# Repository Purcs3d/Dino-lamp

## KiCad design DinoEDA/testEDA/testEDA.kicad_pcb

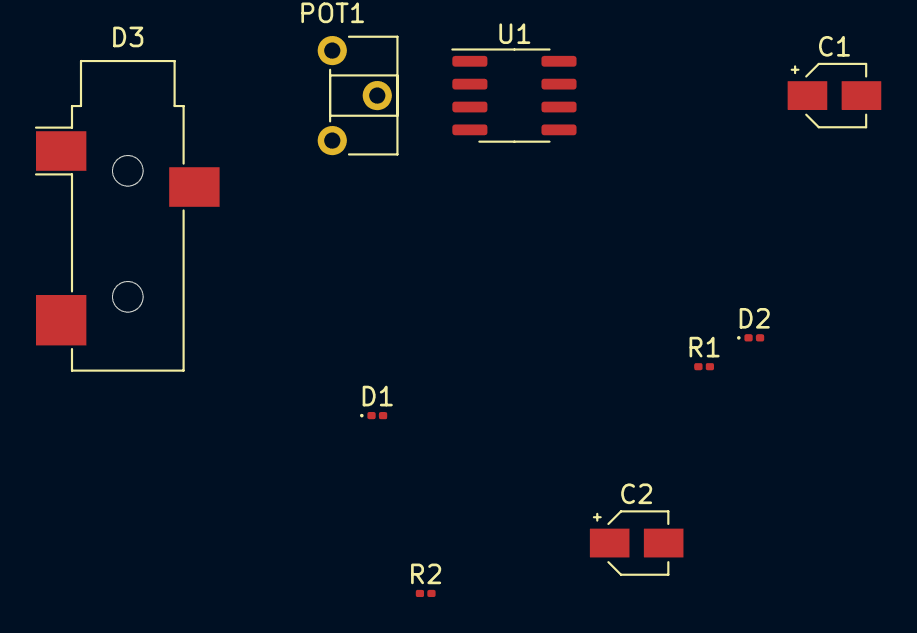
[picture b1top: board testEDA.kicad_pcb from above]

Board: 2 copper layers, 9 parts (0 on the bottom side), 8 nets, no tracks yet.

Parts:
C1: 100nF; CP_Elec_3x5.3
C2: 10nF; CP_Elec_3x5.3
D1, D2: DIODE; D_0201_0603Metric
D3: LED_Series; Jack_3.5mm_CUI_SJ-3523-SMT_Horizontal
POT1: 10K; Potentiometer_ACP_CA6-H2,5_Horizontal
R1: 120; R_0201_0603Metric
R2: 15; R_0201_0603Metric
U1: NE555D; SOIC-8_3.9x4.9mm_P1.27mm

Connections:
+5VD: R1.2, U1.4 (R), U1.8 (VCC)
GND: C1.1, C2.2, U1.1 (GND)
unnamed: C1.2, POT1.2, U1.2 (TR), U1.6 (THR)
unnamed: C2.1, U1.5 (CV)
unnamed: D1.1 (K), D2.2 (A), R1.1, U1.7 (DIS)
unnamed: D1.2 (A), POT1.3
unnamed: D2.1 (K), POT1.1
unnamed: R2.1, U1.3 (Q)

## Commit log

2021-08-31 Init
2021-09-01 EDA added
2022-03-21 Reinit from new device
2022-08-21 General backup
2022-09-01 EDA learning curve
2022-09-02 Still figuring things out
